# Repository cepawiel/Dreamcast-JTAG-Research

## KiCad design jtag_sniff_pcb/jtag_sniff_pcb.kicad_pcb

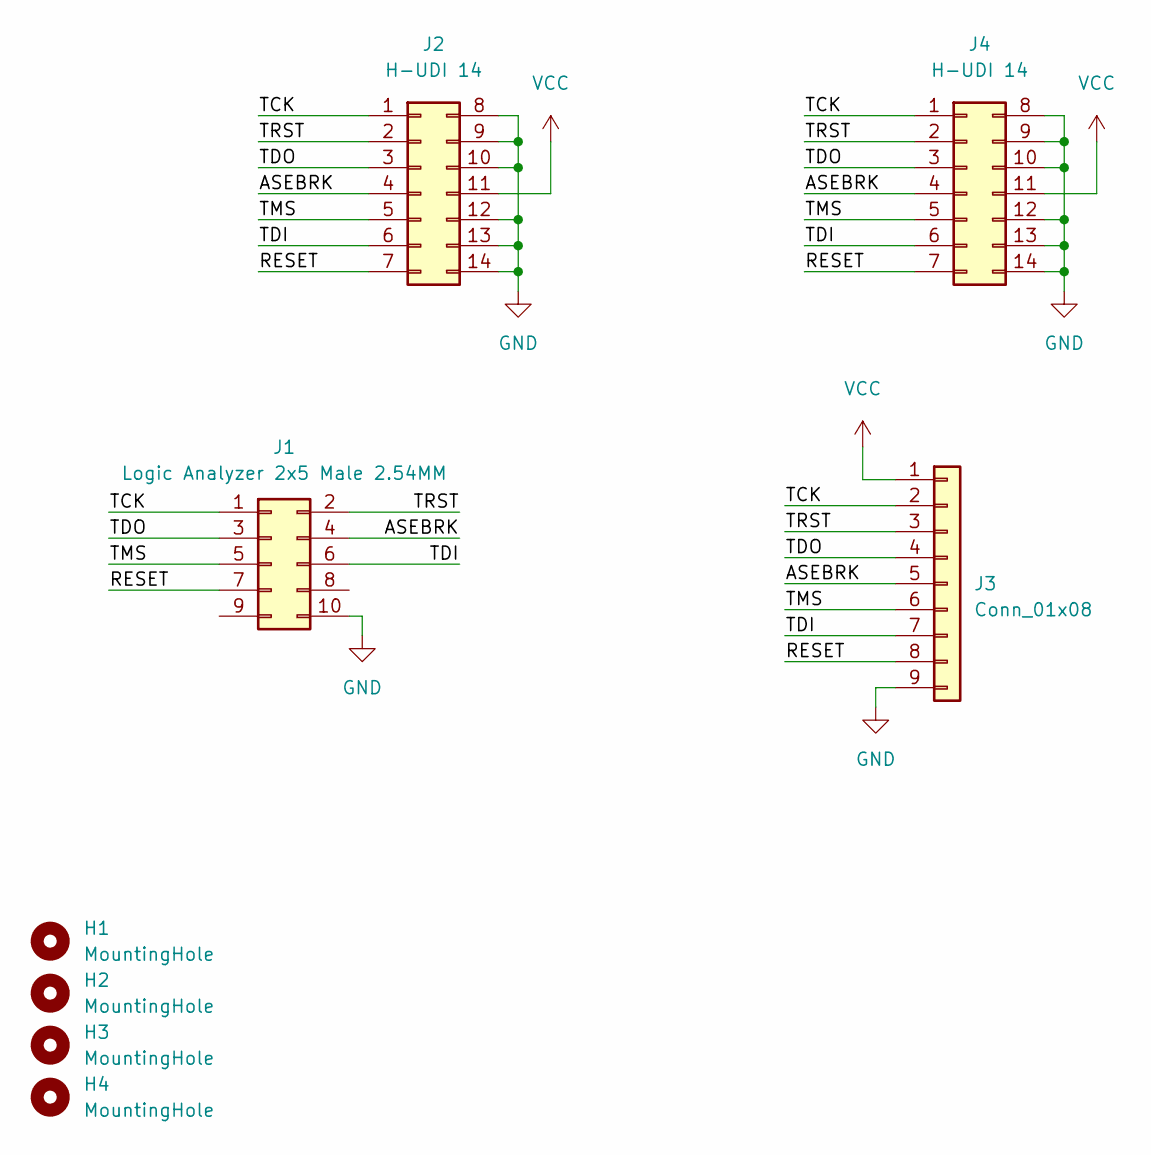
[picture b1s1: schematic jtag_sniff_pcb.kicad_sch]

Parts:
H1, H2, H3, H4: MountingHole; MountingHole_3mm
J1: Logic Analyzer 2x5 Male 2.54MM; PinSocket_2x05_P2.54mm_Vertical
J2, J4: H-UDI 14
J3: Conn_01x08; PinSocket_1x09_P2.54mm_Vertical

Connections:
/ASEBRK: J1.4, J2.4, J3.5, J4.4
/RESET: J1.7, J2.7, J3.8, J4.7
/TCK: J1.1, J2.1, J3.2, J4.1
/TDI: J1.6, J2.6, J3.7, J4.6
/TDO: J1.3, J2.3, J3.4, J4.3
/TMS: J1.5, J2.5, J3.6, J4.5
/TRST: J1.2, J2.2, J3.3, J4.2
GND: J1.10, J2.8, J2.9, J2.10, J2.12, J2.13, J2.14, J3.9, J4.8, J4.9, J4.10, J4.12, J4.13, J4.14
VCC: J2.11, J3.1, J4.11

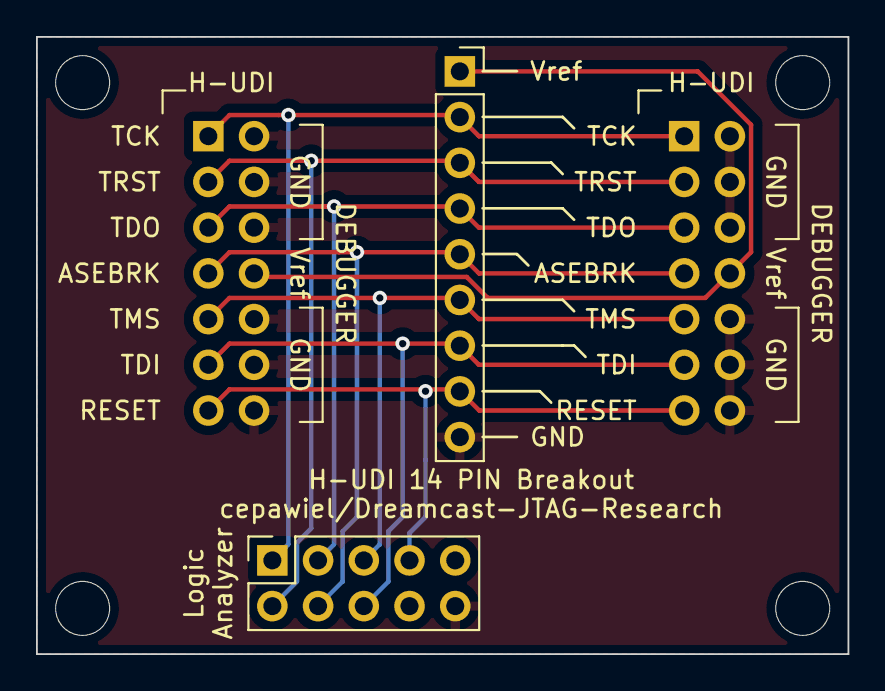
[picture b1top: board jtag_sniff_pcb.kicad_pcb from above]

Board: 2 copper layers, 45.1 x 34.3 mm, 8 parts (0 on the bottom side), 9 nets.
